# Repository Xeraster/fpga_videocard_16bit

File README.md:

# 16 bit fpga driven video card

### ISA interface ports:
- 0x423. settings register
- 0x426 - status register
- 0x428 address pointer low byte register (can also recieve 16 bit isa data cycles)
- 0x429 address pointer middle byte register
- 0x42A address pointer high byte register
- 0x42C data register

# what it does right now
It displays a 640x480 signal with 16 bit color depth. It also has a mostly working ISA interface. The video signal is far from perfect. This code is the synchronous version and is a lot buggier and doesn't work nearly as well. It is generally easy, with the synchronous version, to EITHER solve screen wobble OR incorrect colors but not both. In this particular git push, the colors get incorrect and messed up but screen wobble artifacts happen extremely rarely.

The pixel clock is 25.175MHz and the pll clock is 75.525MHz.

Here is an example of it outputting something. The asynchronous pll clock version has a terrible screen wobble bug (as the only major bug) so do not be fooled by what appears to be a good signal.

Here is a test pattern

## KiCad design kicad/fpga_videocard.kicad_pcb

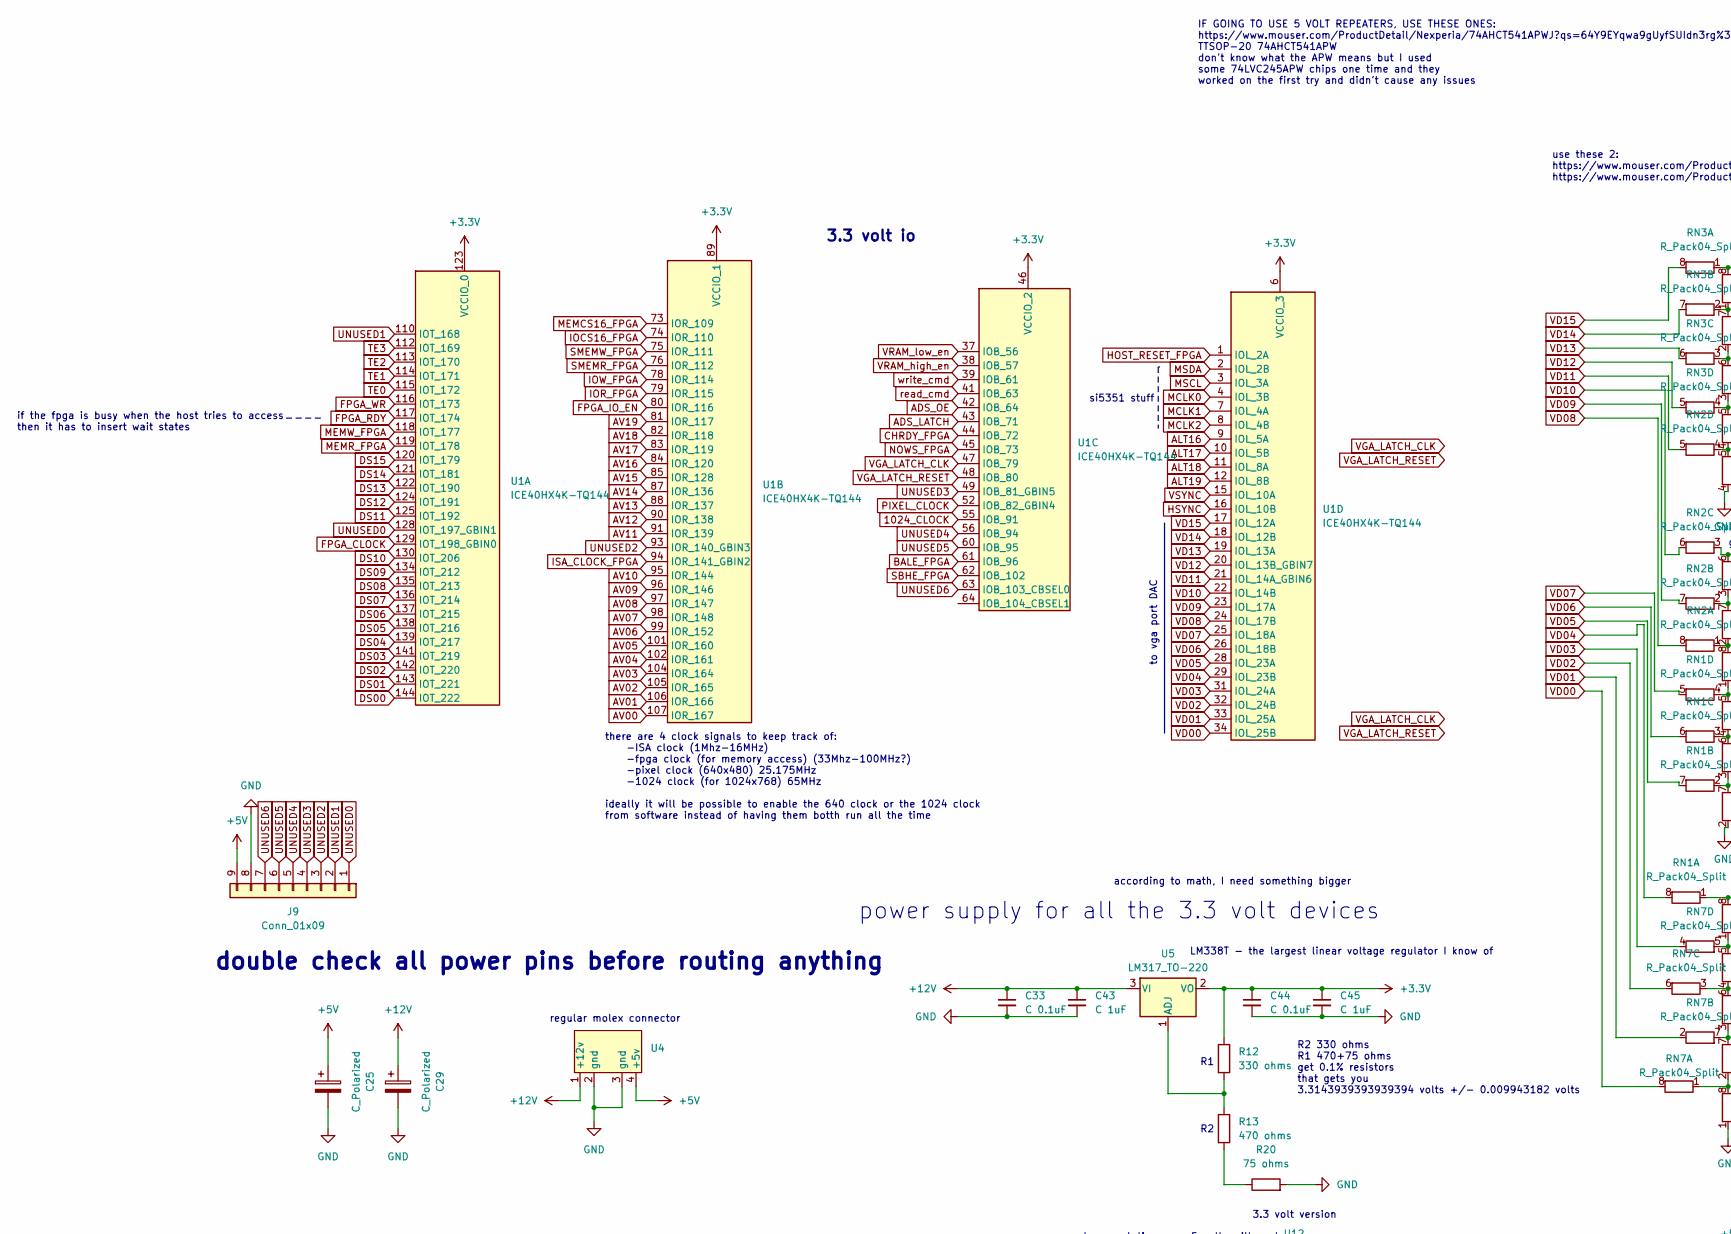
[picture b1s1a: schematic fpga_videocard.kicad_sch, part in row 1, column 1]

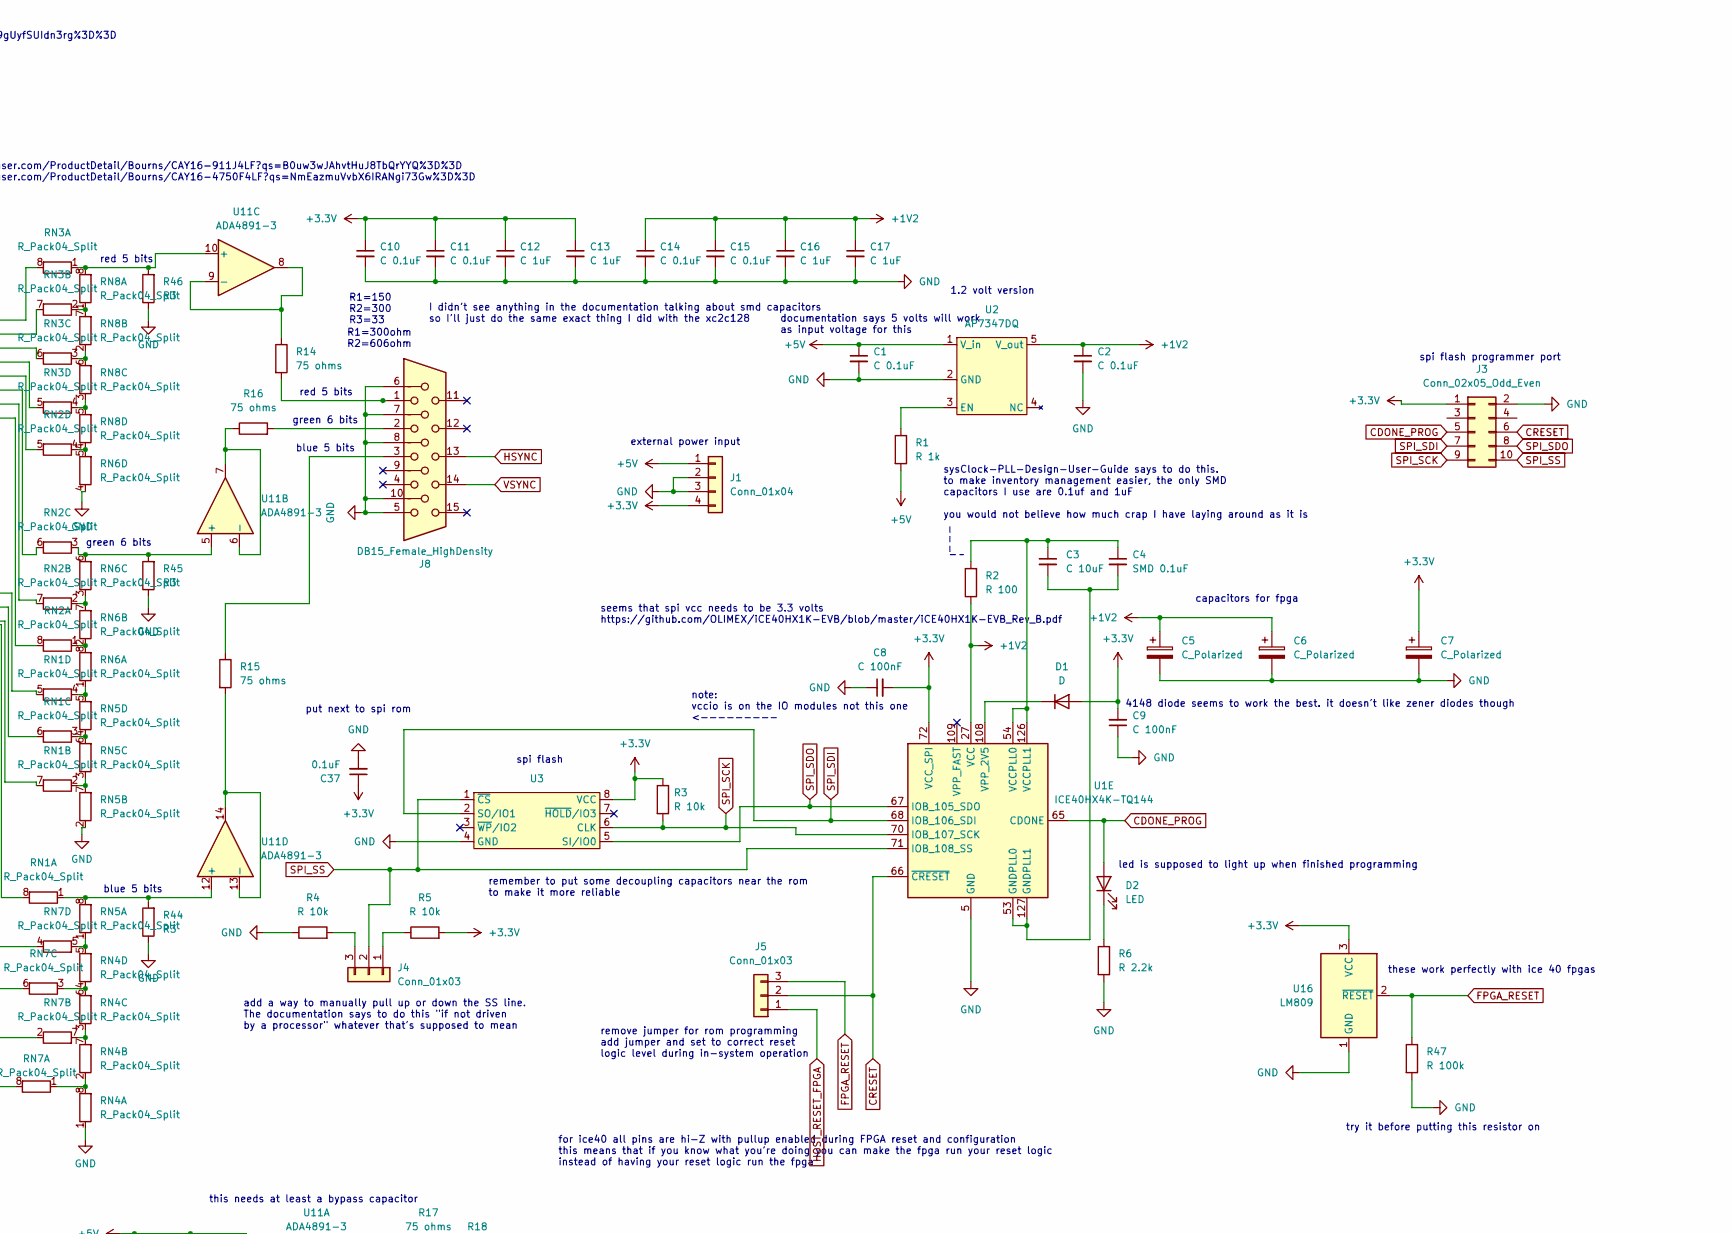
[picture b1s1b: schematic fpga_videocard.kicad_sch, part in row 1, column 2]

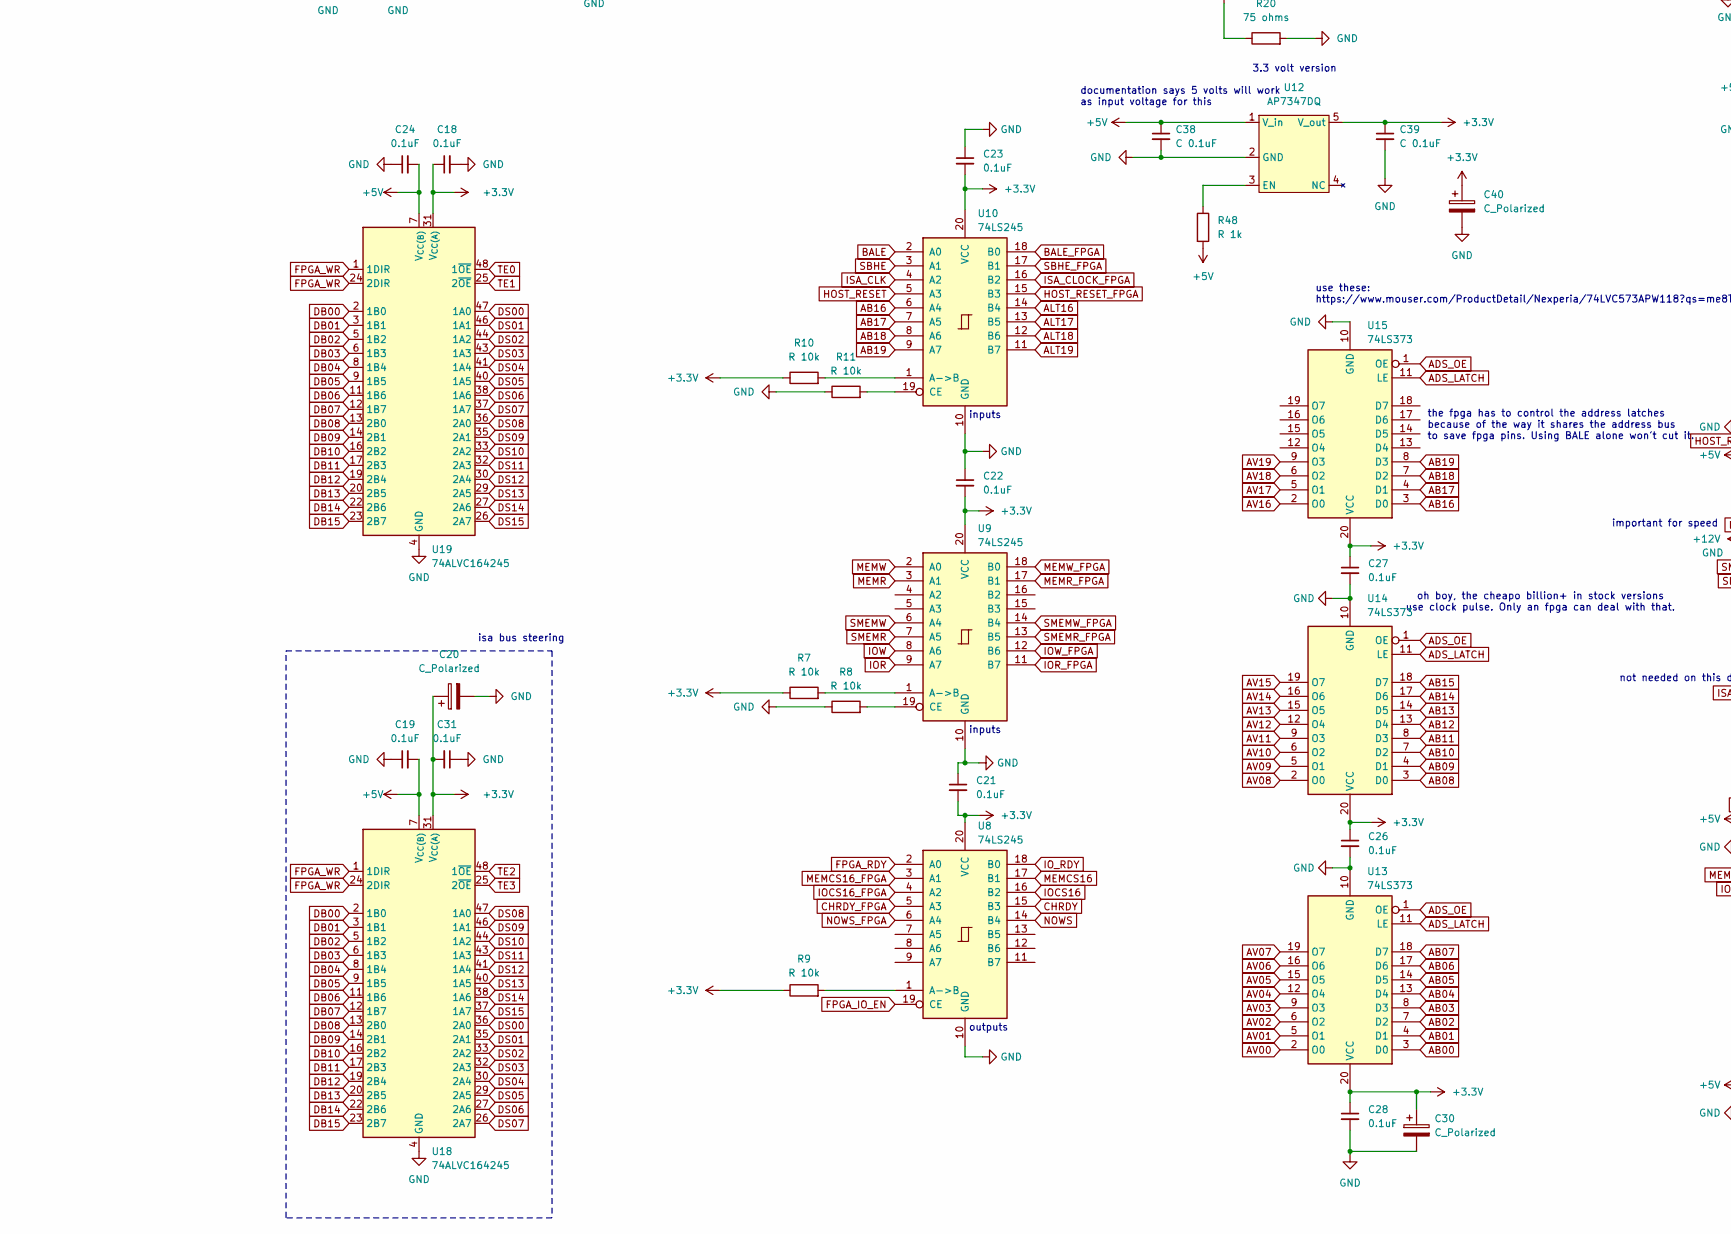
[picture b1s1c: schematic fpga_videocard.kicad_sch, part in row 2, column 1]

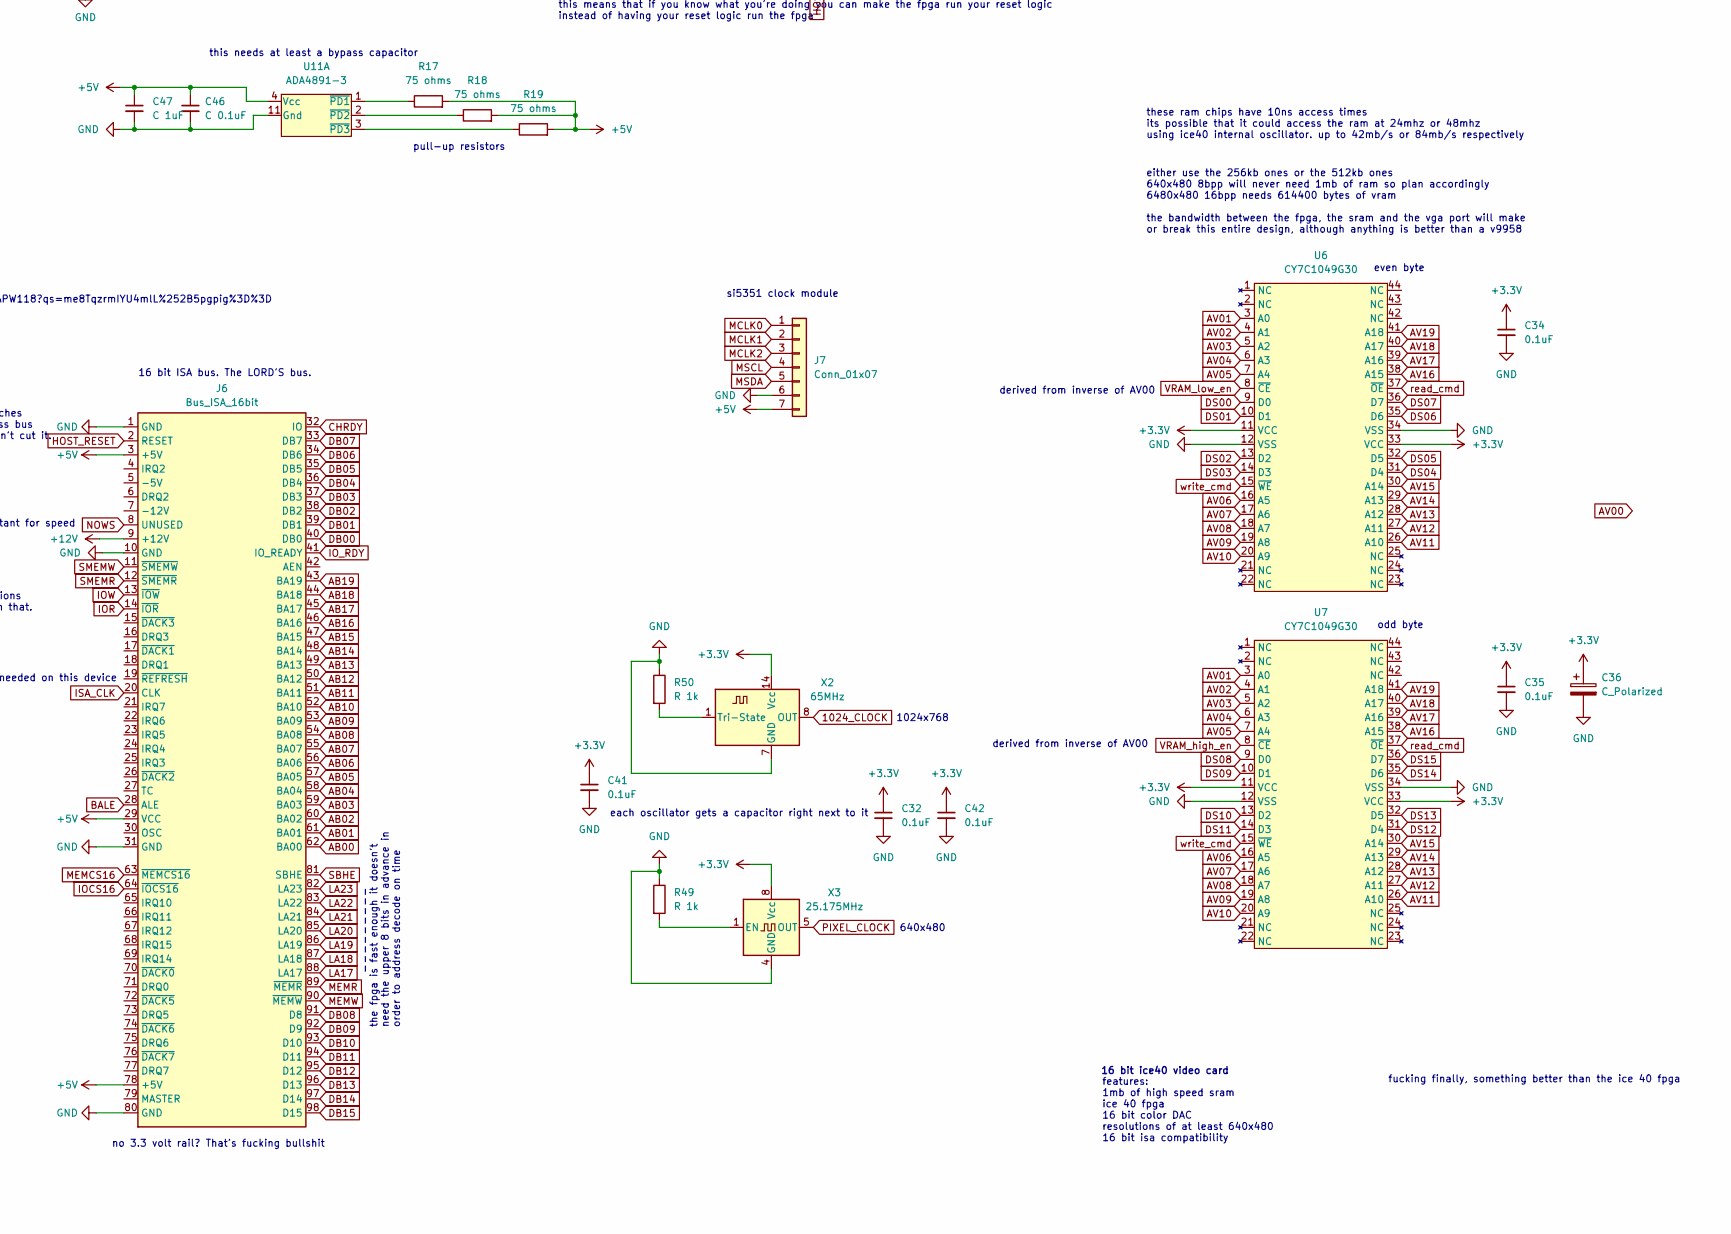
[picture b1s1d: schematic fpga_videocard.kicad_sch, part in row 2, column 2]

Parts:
C1, C2, C10, C11, C14, C15, C38, C39: C 0.1uF; C_1206_3216Metric
C3: C 10uF; C_1206_3216Metric
C4: SMD 0.1uF; C_1206_3216Metric
C5, C6, C7, C20, C25, C29, C40: C_Polarized; CP_Radial_D5.0mm_P2.50mm
C8, C9: C 100nF; C_Disc_D4.3mm_W1.9mm_P5.00mm
C12, C13, C16, C17: C 1uF; C_1206_3216Metric
C18, C19, C21, C22, C23, C24, C26, C27, C28, C31, C32, C34, C35, C37, C41, C42: 0.1uF; C_1206_3216Metric_Pad1.33x1.80mm_HandSolder
C30, C36: C_Polarized; CP_Radial_D4.0mm_P2.00mm
C33, C44, C46: C 0.1uF; C_1206_3216Metric_Pad1.33x1.80mm_HandSolder
C43, C45, C47: C 1uF; C_1206_3216Metric_Pad1.33x1.80mm_HandSolder
D1: D; D_DO-34_SOD68_P7.62mm_Horizontal
D2: LED; LED_D5.0mm
J1: Conn_01x04; PinHeader_1x04_P2.54mm_Vertical
J3: Conn_02x05_Odd_Even; PinHeader_2x05_P2.54mm_Vertical
J4, J5: Conn_01x03; PinHeader_1x03_P2.54mm_Vertical
J6: Bus_ISA_16bit; BUS_AT
J7: Conn_01x07; PinHeader_1x07_P2.54mm_Vertical
J8: DB15_Female_HighDensity; DSUB-15-HD_Female_Horizontal_P2.29x1.98mm_EdgePinOffset3.03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
J9: Conn_01x09; PinHeader_1x09_P2.54mm_Vertical
R1, R48, R49, R50: R 1k; R_Axial_DIN0207_L6.3mm_D2.5mm_P10.16mm_Horizontal
R2: R 100; R_Axial_DIN0207_L6.3mm_D2.5mm_P10.16mm_Horizontal
R3, R4, R5, R7, R8, R9, R10, R11: R 10k; R_0805_2012Metric_Pad1.20x1.40mm_HandSolder
R6: R 2.2k; R_Axial_DIN0207_L6.3mm_D2.5mm_P10.16mm_Horizontal
R12: 330 ohms; R_0805_2012Metric_Pad1.20x1.40mm_HandSolder
R13: 470 ohms; R_0805_2012Metric_Pad1.20x1.40mm_HandSolder
R14, R15, R16, R17, R18, R19, R20: 75 ohms; R_0805_2012Metric_Pad1.20x1.40mm_HandSolder
R44, R45, R46: R3; R_0805_2012Metric_Pad1.20x1.40mm_HandSolder
R47: R 100k; R_Axial_DIN0207_L6.3mm_D2.5mm_P10.16mm_Horizontal
RN1, RN2, RN3, RN4, RN5, RN6, RN7, RN8: R_Pack04_Split; R_Array_Convex_4x1206
U1: ICE40HX4K-TQ144; TQFP-144_20x20mm_P0.5mm
U2, U12: AP7347DQ; SOT-23-5
U3: SOIC-8_5.275x5.275mm_P1.27mm
U4: Mouser_Molex
U5: LM317_TO-220; TO-220-3_Vertical
U6, U7: CY7C1049G30; TSOP-44
U8, U9, U10: 74LS245; TSSOP-20_4.4x6.5mm_P0.65mm
U11: ADA4891-3; TSSOP-14_4.4x5mm_P0.65mm
U13, U14, U15: 74LS373; TSSOP-20_4.4x6.5mm_P0.65mm
U16: LM809; SOT-23
U18, U19: 74ALVC164245; TSSOP-48_6.1x12.5mm_P0.5mm
X2: 65MHz; Oscillator_DIP-14
X3: 25.175MHz; Oscillator_DIP-8

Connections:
1024_CLOCK: U1.55 (IOB_91), X2.8 (OUT)
+1V2: C2.1, C5.1, C6.1, C14.1, C15.1, C16.1, C17.1, R2.1, U1.27 (VCC), U1.40 (VCC), U1.92 (VCC), U1.111 (VCC), U2.5 (V_out)
+3.3V: C7.1, C8.2, C9.2, C10.1, C11.1, C12.1, C13.1, C18.1, C20.1, C21.2, C22.2, C23.2, C26.1, C27.1, C28.1, C30.1, C31.2, C32.1, C34.1, C35.1, C36.1, C37.1, C39.1, C40.1, C41.1, C42.1, C44.1, C45.1, D1.2 (A), J1.4, J3.1, R3.1, R5.2, R7.1, R9.1, R10.1, R12.1, U1.6 (VCCIO_3), U1.30 (VCCIO_3), U1.46 (VCCIO_2), U1.57 (VCCIO_2), U1.72 (VCC_SPI), U1.89 (VCCIO_1), U1.100 (VCCIO_1), U1.123 (VCCIO_0), U1.131 (VCCIO_0), U3.8 (VCC), U5.2 (VO), U6.11 (VCC), U6.33 (VCC), U7.11 (VCC), U7.33 (VCC), U8.20 (VCC), U9.20 (VCC), U10.20 (VCC), U12.5 (V_out), U13.20 (VCC), U14.20 (VCC), U15.20 (VCC), U16.3 (VCC), U18.31 (V_{CC(A)}), U18.42 (V_{CC(A)}), U19.31 (V_{CC(A)}), U19.42 (V_{CC(A)}), X2.14 (Vcc), X3.8 (Vcc)
+5V: C1.1, C19.2, C24.2, C25.1, C38.1, C46.1, C47.1, J1.1, J6.3 (+5V), J6.29 (VCC), J6.78 (+5V), J7.7, J9.9, R1.2, R17.2, R18.2, R19.2, R48.2, U2.1 (V_in), U4.4 (+5v), U11.4 (Vcc), U12.1 (V_in), U18.7 (V_{CC(B)}), U18.18 (V_{CC(B)}), U19.7 (V_{CC(B)}), U19.18 (V_{CC(B)})
+12V: C29.1, C33.1, C43.1, J6.9 (+12V), U4.1 (+12v), U5.3 (VI)
AB00: J6.62 (BA00), U13.3 (D0)
AB01: J6.61 (BA01), U13.4 (D1)
AB02: J6.60 (BA02), U13.7 (D2)
AB03: J6.59 (BA03), U13.8 (D3)
AB04: J6.58 (BA04), U13.13 (D4)
AB05: J6.57 (BA05), U13.14 (D5)
AB06: J6.56 (BA06), U13.17 (D6)
AB07: J6.55 (BA07), U13.18 (D7)
AB08: J6.54 (BA08), U14.3 (D0)
AB09: J6.53 (BA09), U14.4 (D1)
AB10: J6.52 (BA10), U14.7 (D2)
AB11: J6.51 (BA11), U14.8 (D3)
AB12: J6.50 (BA12), U14.13 (D4)
AB13: J6.49 (BA13), U14.14 (D5)
AB14: J6.48 (BA14), U14.17 (D6)
AB15: J6.47 (BA15), U14.18 (D7)
AB16: J6.46 (BA16), U10.6 (A4), U15.3 (D0)
AB17: J6.45 (BA17), U10.7 (A5), U15.4 (D1)
AB18: J6.44 (BA18), U10.8 (A6), U15.7 (D2)
AB19: J6.43 (BA19), U10.9 (A7), U15.8 (D3)
ADS_LATCH: U1.43 (IOB_71), U13.11 (LE), U14.11 (LE), U15.11 (LE)
ADS_OE: U1.42 (IOB_64), U13.1 (OE), U14.1 (OE), U15.1 (OE)
ALT16: U1.9 (IOL_5A), U10.14 (B4)
ALT17: U1.10 (IOL_5B), U10.13 (B5)
ALT18: U1.11 (IOL_8A), U10.12 (B6)
ALT19: U1.12 (IOL_8B), U10.11 (B7)
AV00: U1.107 (IOR_167), U13.2 (O0)
AV01: U1.106 (IOR_166), U6.3 (A0), U7.3 (A0), U13.5 (O1)
AV02: U1.105 (IOR_165), U6.4 (A1), U7.4 (A1), U13.6 (O2)
AV03: U1.104 (IOR_164), U6.5 (A2), U7.5 (A2), U13.9 (O3)
AV04: U1.102 (IOR_161), U6.6 (A3), U7.6 (A3), U13.12 (O4)
AV05: U1.101 (IOR_160), U6.7 (A4), U7.7 (A4), U13.15 (O5)
AV06: U1.99 (IOR_152), U6.16 (A5), U7.16 (A5), U13.16 (O6)
AV07: U1.98 (IOR_148), U6.17 (A6), U7.17 (A6), U13.19 (O7)
AV08: U1.97 (IOR_147), U6.18 (A7), U7.18 (A7), U14.2 (O0)
AV09: U1.96 (IOR_146), U6.19 (A8), U7.19 (A8), U14.5 (O1)
AV10: U1.95 (IOR_144), U6.20 (A9), U7.20 (A9), U14.6 (O2)
AV11: U1.91 (IOR_139), U6.26 (A10), U7.26 (A10), U14.9 (O3)
AV12: U1.90 (IOR_138), U6.27 (A11), U7.27 (A11), U14.12 (O4)
AV13: U1.88 (IOR_137), U6.28 (A12), U7.28 (A12), U14.15 (O5)
AV14: U1.87 (IOR_136), U6.29 (A13), U7.29 (A13), U14.16 (O6)
AV15: U1.85 (IOR_128), U6.30 (A14), U7.30 (A14), U14.19 (O7)
AV16: U1.84 (IOR_120), U6.38 (A15), U7.38 (A15), U15.2 (O0)
AV17: U1.83 (IOR_119), U6.39 (A16), U7.39 (A16), U15.5 (O1)
AV18: U1.82 (IOR_118), U6.40 (A17), U7.40 (A17), U15.6 (O2)
AV19: U1.81 (IOR_117), U6.41 (A18), U7.41 (A18), U15.9 (O3)
BALE: J6.28 (ALE), U10.2 (A0)
BALE_FPGA: U1.61 (IOB_96), U10.18 (B0)
CDONE_PROG: D2.2 (A), J3.5, U1.65 (CDONE)
CHRDY: J6.32 (IO), U8.15 (B3)
CHRDY_FPGA: U1.44 (IOB_72), U8.5 (A3)
CRESET: J3.6, J5.2, U1.66 (~CRESET)
DB00: J6.40 (DB0), U18.2 (1B0), U19.2 (1B0)
DB01: J6.39 (DB1), U18.3 (1B1), U19.3 (1B1)
DB02: J6.38 (DB2), U18.5 (1B2), U19.5 (1B2)
DB03: J6.37 (DB3), U18.6 (1B3), U19.6 (1B3)
DB04: J6.36 (DB4), U18.8 (1B4), U19.8 (1B4)
DB05: J6.35 (DB5), U18.9 (1B5), U19.9 (1B5)
DB06: J6.34 (DB6), U18.11 (1B6), U19.11 (1B6)
DB07: J6.33 (DB7), U18.12 (1B7), U19.12 (1B7)
DB08: J6.91 (D8), U18.13 (2B0), U19.13 (2B0)
DB09: J6.92 (D9), U18.14 (2B1), U19.14 (2B1)
DB10: J6.93 (D10), U18.16 (2B2), U19.16 (2B2)
DB11: J6.94 (D11), U18.17 (2B3), U19.17 (2B3)
DB12: J6.95 (D12), U18.19 (2B4), U19.19 (2B4)
DB13: J6.96 (D13), U18.20 (2B5), U19.20 (2B5)
DB14: J6.97 (D14), U18.22 (2B6), U19.22 (2B6)
DB15: J6.98 (D15), U18.23 (2B7), U19.23 (2B7)
DS00: U1.144 (IOT_222), U6.9 (D0), U18.36 (2A0), U19.47 (1A0)
DS01: U1.143 (IOT_221), U6.10 (D1), U18.35 (2A1), U19.46 (1A1)
DS02: U1.142 (IOT_220), U6.13 (D2), U18.33 (2A2), U19.44 (1A2)
DS03: U1.141 (IOT_219), U6.14 (D3), U18.32 (2A3), U19.43 (1A3)
DS04: U1.139 (IOT_217), U6.31 (D4), U18.30 (2A4), U19.41 (1A4)
DS05: U1.138 (IOT_216), U6.32 (D5), U18.29 (2A5), U19.40 (1A5)
DS06: U1.137 (IOT_215), U6.35 (D6), U18.27 (2A6), U19.38 (1A6)
DS07: U1.136 (IOT_214), U6.36 (D7), U18.26 (2A7), U19.37 (1A7)
DS08: U1.135 (IOT_213), U7.9 (D0), U18.47 (1A0), U19.36 (2A0)
DS09: U1.134 (IOT_212), U7.10 (D1), U18.46 (1A1), U19.35 (2A1)
DS10: U1.130 (IOT_206), U7.13 (D2), U18.44 (1A2), U19.33 (2A2)
DS11: U1.125 (IOT_192), U7.14 (D3), U18.43 (1A3), U19.32 (2A3)
DS12: U1.124 (IOT_191), U7.31 (D4), U18.41 (1A4), U19.30 (2A4)
DS13: U1.122 (IOT_190), U7.32 (D5), U18.40 (1A5), U19.29 (2A5)
DS14: U1.121 (IOT_181), U7.35 (D6), U18.38 (1A6), U19.27 (2A6)
DS15: U1.120 (IOT_179), U7.36 (D7), U18.37 (1A7), U19.26 (2A7)
FPGA_CLOCK: U1.129 (IOT_198_GBIN0)
FPGA_IO_EN: U1.80 (IOR_116), U8.19 (CE)
FPGA_RDY: U1.117 (IOT_174), U8.2 (A0)
FPGA_RESET: J5.3, R47.1, U16.2 (~RESET)
FPGA_WR: U1.116 (IOT_173), U18.1 (1DIR), U18.24 (2DIR), U19.1 (1DIR), U19.24 (2DIR)
GND: C1.2, C2.2, C5.2, C6.2, C7.2, C8.1, C9.1, C10.2, C11.2, C12.2, C13.2, C14.2, C15.2, C16.2, C17.2, C18.2, C19.1, C20.2, C21.1, C22.1, C23.1, C24.1, C25.2, C26.2, C27.2, C28.2, C29.2, C30.2, C31.1, C32.2, C33.2, C34.2, C35.2, C36.2, C37.2, C38.2, C39.2, C40.2, C41.2, C42.2, C43.2, C44.2, C45.2, C46.2, C47.2, J1.2, J1.3, J3.2, J6.1 (GND), J6.10 (GND), J6.31 (GND), J6.80 (GND), J7.6, J8.5, J8.6, J8.7, J8.8, J8.10, J9.8, R4.1, R6.2, R8.1, R11.1, R20.2, R44.1, R45.1, R46.1, R47.2, R49.1, R50.1, RN4.1 (R1.1), RN5.2 (R2.1), RN6.4 (R4.1), U1.5 (GND), U1.13 (GND), U1.14 (GND), U1.59 (GND), U1.69 (GND), U1.86 (GND), U1.103 (GND), U1.132 (GND), U1.140 (GND), U2.2 (GND), U3.4 (GND), U4.2 (gnd), U4.3 (gnd), U6.12 (VSS), U6.34 (VSS), U7.12 (VSS), U7.34 (VSS), U8.10 (GND), U9.10 (GND), U10.10 (GND), U11.11 (Gnd), U12.2 (GND), U13.10 (GND), U14.10 (GND), U15.10 (GND), U16.1 (GND), U18.4 (GND), U18.10 (GND), U18.15 (GND), U18.21 (GND), U18.28 (GND), U18.34 (GND), U18.39 (GND), U18.45 (GND), U19.4 (GND), U19.10 (GND), U19.15 (GND), U19.21 (GND), U19.28 (GND), U19.34 (GND), U19.39 (GND), U19.45 (GND), X2.7 (GND), X3.4 (GND)
HOST_RESET: J6.2 (RESET), U10.5 (A3)
HOST_RESET_FPGA: J5.1, U1.1 (IOL_2A), U10.15 (B3)
HSYNC: J8.13, U1.16 (IOL_10B)
IOCS16: J6.64 (~IOCS16), U8.16 (B2)
IOCS16_FPGA: U1.74 (IOR_110), U8.4 (A2)
IOR: J6.14 (~IOR), U9.9 (A7)
IOR_FPGA: U1.79 (IOR_115), U9.11 (B7)
IOW: J6.13 (~IOW), U9.8 (A6)
IOW_FPGA: U1.78 (IOR_114), U9.12 (B6)
IO_RDY: J6.41 (IO_READY), U8.18 (B0)
ISA_CLK: J6.20 (CLK), U10.4 (A2)
ISA_CLOCK_FPGA: U1.94 (IOR_141_GBIN2), U10.16 (B2)
LA17: J6.88 (LA17)
LA18: J6.87 (LA18)
LA19: J6.86 (LA19)
LA20: J6.85 (LA20)
LA21: J6.84 (LA21)
LA22: J6.83 (LA22)
LA23: J6.82 (LA23)
MCLK0: J7.1, U1.4 (IOL_3B)
MCLK1: J7.2, U1.7 (IOL_4A)
MCLK2: J7.3, U1.8 (IOL_4B)
MEMCS16: J6.63 (~MEMCS16), U8.17 (B1)
MEMCS16_FPGA: U1.73 (IOR_109), U8.3 (A1)
MEMR: J6.89 (~MEMR), U9.3 (A1)
MEMR_FPGA: U1.119 (IOT_178), U9.17 (B1)
MEMW: J6.90 (~MEMW), U9.2 (A0)
MEMW_FPGA: U1.118 (IOT_177), U9.18 (B0)
MSCL: J7.4, U1.3 (IOL_3A)
MSDA: J7.5, U1.2 (IOL_2B)
NOWS: J6.8 (UNUSED), U8.14 (B4)
NOWS_FPGA: U1.45 (IOB_73), U8.6 (A4)
unnamed: D1.1 (K), U1.108 (VPP_2V5)
unnamed: D2.1 (K), R6.1
unnamed: J4.1, R5.1
unnamed: J4.3, R4.2
unnamed: J8.1, R14.2
unnamed: J8.2, R16.2
unnamed: J8.3, R15.1
unnamed: R13.2, R20.1
unnamed: R44.2, RN1.1 (R1.1), RN5.8 (R1.2), U11.12 (+)
unnamed: RN1.2 (R2.1), RN5.3 (R3.1), RN5.7 (R2.2)
unnamed: RN1.3 (R3.1), RN5.4 (R4.1), RN5.6 (R3.2)
unnamed: RN1.4 (R4.1), RN5.5 (R4.2), RN6.1 (R1.1)
unnamed: RN2.1 (R1.1), RN6.2 (R2.1), RN6.8 (R1.2)
unnamed: RN2.2 (R2.1), RN6.3 (R3.1), RN6.7 (R2.2)
unnamed: R45.2, RN2.3 (R3.1), RN6.6 (R3.2), U11.5 (+)
unnamed: RN2.4 (R4.1), RN6.5 (R4.2), RN8.4 (R4.1)
unnamed: R46.2, RN3.1 (R1.1), RN8.8 (R1.2), U11.10 (+)
unnamed: RN3.2 (R2.1), RN8.1 (R1.1), RN8.7 (R2.2)
unnamed: RN3.3 (R3.1), RN8.2 (R2.1), RN8.6 (R3.2)
unnamed: RN3.4 (R4.1), RN8.3 (R3.1), RN8.5 (R4.2)
unnamed: RN4.2 (R2.1), RN4.8 (R1.2), RN7.1 (R1.1)
unnamed: RN4.3 (R3.1), RN4.7 (R2.2), RN7.7 (R2.2)
unnamed: RN4.4 (R4.1), RN4.6 (R3.2), RN7.3 (R3.1)
unnamed: RN4.5 (R4.2), RN5.1 (R1.1), RN7.5 (R4.2)
unnamed: C3.2, C4.2, U1.53 (GNDPLL0), U1.127 (GNDPLL1)
unnamed: C3.1, C4.1, R2.2, U1.54 (VCCPLL0), U1.126 (VCCPLL1)
unnamed: R1.1, U2.3 (EN)
unnamed: R12.2, R13.1, U5.1 (ADJ)
unnamed: R9.2, U8.1 (A->B)
unnamed: R7.2, U9.1 (A->B)
unnamed: R8.2, U9.19 (CE)
unnamed: R10.2, U10.1 (A->B)
unnamed: R11.2, U10.19 (CE)
unnamed: R17.1, U11.1 (~PD1)
unnamed: R18.1, U11.2 (~PD2)
unnamed: R19.1, U11.3 (~PD3)
unnamed: R16.1, U11.6 (-), U11.7
unnamed: R14.1, U11.8, U11.9 (-)
unnamed: R15.2, U11.13 (-), U11.14
unnamed: R48.1, U12.3 (EN)
unnamed: R50.2, X2.1 (Tri-State)
unnamed: R49.2, X3.1 (EN)
PIXEL_CLOCK: U1.52 (IOB_82_GBIN4), X3.5 (OUT)
SBHE: J6.81 (SBHE), U10.3 (A1)
SBHE_FPGA: U1.62 (IOB_102), U10.17 (B1)
SMEMR: J6.12 (~SMEMR), U9.7 (A5)
SMEMR_FPGA: U1.76 (IOR_112), U9.13 (B5)
SMEMW: J6.11 (~SMEMW), U9.6 (A4)
SMEMW_FPGA: U1.75 (IOR_111), U9.14 (B4)
SPI_SCK: J3.9, R3.2, U1.70 (IOB_107_SCK), U3.6 (CLK)
SPI_SDI: J3.7, U1.68 (IOB_106_SDI), U3.2 (SO/IO1)
SPI_SDO: J3.8, U1.67 (IOB_105_SDO), U3.5 (SI/IO0)
SPI_SS: J3.10, J4.2, U1.71 (IOB_108_SS), U3.1 (~CS)
TE0: U1.115 (IOT_172), U19.48 (1~OE)
TE1: U1.114 (IOT_171), U19.25 (2~OE)
TE2: U1.113 (IOT_170), U18.48 (1~OE)
TE3: U1.112 (IOT_169), U18.25 (2~OE)
UNUSED0: J9.1, U1.128 (IOT_197_GBIN1)
UNUSED1: J9.2, U1.110 (IOT_168)
UNUSED2: J9.3, U1.93 (IOR_140_GBIN3)
UNUSED3: J9.4, U1.49 (IOB_81_GBIN5)
UNUSED4: J9.5, U1.56 (IOB_94)
UNUSED5: J9.6, U1.60 (IOB_95)
UNUSED6: J9.7, U1.63 (IOB_103_CBSEL0)
VD00: RN7.8 (R1.2), U1.34 (IOL_25B)
VD01: RN7.2 (R2.1), U1.33 (IOL_25A)
VD02: RN7.6 (R3.2), U1.32 (IOL_24B)
VD03: RN7.4 (R4.1), U1.31 (IOL_24A)
VD04: RN1.8 (R1.2), U1.29 (IOL_23B)
VD05: RN1.7 (R2.2), U1.28 (IOL_23A)
VD06: RN1.6 (R3.2), U1.26 (IOL_18B)
VD07: RN1.5 (R4.2), U1.25 (IOL_18A)
VD08: RN2.8 (R1.2), U1.24 (IOL_17B)
VD09: RN2.7 (R2.2), U1.23 (IOL_17A)
VD10: RN2.6 (R3.2), U1.22 (IOL_14B)
VD11: RN2.5 (R4.2), U1.21 (IOL_14A_GBIN6)
VD12: RN3.5 (R4.2), U1.20 (IOL_13B_GBIN7)
VD13: RN3.6 (R3.2), U1.19 (IOL_13A)
VD14: RN3.7 (R2.2), U1.18 (IOL_12B)
VD15: RN3.8 (R1.2), U1.17 (IOL_12A)
VGA_LATCH_CLK: U1.47 (IOB_79)
VGA_LATCH_RESET: U1.48 (IOB_80)
VRAM_high_en: U1.38 (IOB_57), U7.8 (~CE)
VRAM_low_en: U1.37 (IOB_56), U6.8 (~CE)
VSYNC: J8.14, U1.15 (IOL_10A)
read_cmd: U1.41 (IOB_63), U6.37 (~OE), U7.37 (~OE)
write_cmd: U1.39 (IOB_61), U6.15 (~WE), U7.15 (~WE)

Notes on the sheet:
LM338T - the largest linear voltage regulator I know of
these work perfectly with ice 40 fpgas
red 5 bits
isa bus steering
the fpga has to control the address latches because of the way it shares the address bus to save fpga pins. Using BALE alone won't cut it.
IF GOING TO USE 5 VOLT REPEATERS, USE THESE ONES: https://www.mouser.com/ProductDetail/Nexperia/74AHCT541APWJ?qs=64Y9EYqwa9gUyfSUIdn3rg%3D%3D TTSOP-20 74AHCT541APW don't know what the APW means but I used some 74LVC245APW chips one time and they worked on the first try and didn't cause any issues
even byte
remove jumper for rom programming add jumper and set to correct reset logic level during in-system operation
use these: https://www.mouser.com/ProductDetail/Nexperia/74LVC573APW118?qs=me8TqzrmIYU4mlL%252B5pgpig%3D%3D
these ram chips have 10ns access times its possible that it could access the ram at 24mhz or 48mhz using ice40 internal oscillator. up to 42mb/s or 84mb/s respectively
try it before putting this resistor on
R1=300ohm R2=606ohm
sysClock-PLL-Design-User-Guide says to do this. to make inventory management easier, the only SMD capacitors I use are 0.1uf and 1uF you would not believe how much crap I have laying around as it is
spi flash
si5351 stuff
according to math, I need something bigger
regular molex connector
this needs at least a bypass capacitor
to vga port DAC
fucking finally, something better than the ice 40 fpga
use these 2: https://www.mouser.com/ProductDetail/Bourns/CAY16-911J4LF?qs=B0uw3wJAhvtHuJ8TbQrYYQ%3D%3D https://www.mouser.com/ProductDetail/Bourns/CAY16-4750F4LF?qs=NmEazmuVvbX6IRANgi73Gw%3D%3D
no 3.3 volt rail? That's fucking bullshit
1.2 volt version
3.3 volt io
for ice40 all pins are hi-Z with pullup enabled during FPGA reset and configuration this means that if you know what you're doing you can make the fpga run your reset logic instead of having your reset logic run the fpga
blue 5 bits
not needed on this device
note: vccio is on the IO modules not this one <---------
either use the 256kb ones or the 512kb ones 640x480 8bpp will never need 1mb of ram so plan accordingly 6480x480 16bpp needs 614400 bytes of vram the bandwidth between the fpga, the sram and the vga port will make or break this entire design, although anything is better than a v9958
double check all power pins before routing anything
led is supposed to light up when finished programming
if the fpga is busy when the host tries to access then it has to insert wait states
external power input
inputs
16 bit ice40 video card
put next to spi rom
power supply for all the 3.3 volt devices
green 6 bits
seems that spi vcc needs to be 3.3 volts https://github.com/OLIMEX/iCE40HX1K-EVB/blob/master/iCE40HX1K-EVB_Rev_B.pdf
pull-up resistors

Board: 4 copper layers, 112 parts (0 on the bottom side), 204 nets, no tracks yet.

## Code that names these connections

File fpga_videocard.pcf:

set_io pixelClock 52
#set_io clock1024 55
set_io HOST_RESET 1
set_io HSYNC 16
set_io VSYNC 15

#vga output bits
set_io Red[0] 21    #VD11
set_io Red[1] 128    #use this pin instead because of a routing mistake
set_io Red[2] 19
set_io Red[3] 18
set_io Red[4] 17    #VD15

set_io Green[0] 28    #VD05
set_io Green[1] 26
set_io Green[2] 25
set_io Green[3] 24
set_io Green[4] 23
set_io Green[5] 22    #VD10

set_io Blue[0] 34    #VD00
set_io Blue[1] 33
set_io Blue[2] 32
set_io Blue[3] 31
set_io Blue[4] 29    #VD04

#vram address bus
set_io AV[0] 107
set_io AV[1] 106
set_io AV[2] 105
set_io AV[3] 104
set_io AV[4] 102
set_io AV[5] 101
set_io AV[6] 99
set_io AV[7] 98
set_io AV[8] 97
set_io AV[9] 96
set_io AV[10] 95
set_io AV[11] 91
set_io AV[12] 90
set_io AV[13] 88
set_io AV[14] 87
set_io AV[15] 85
set_io AV[16] 84
set_io AV[17] 83
set_io AV[18] 82
set_io AV[19] 81

#16 bit vram data bus
set_io DS[0] 144
set_io DS[1] 143
set_io DS[2] 142
set_io DS[3] 141
set_io DS[4] 139
set_io DS[5] 138
set_io DS[6] 137
set_io DS[7] 136
set_io DS[8] 135
set_io DS[9] 134
set_io DS[10] 130
set_io DS[11] 125
set_io DS[12] 124
set_io DS[13] 122
set_io DS[14] 121
set_io DS[15] 120

#sram chip control signals
set_io read_cmd 41
set_io write_cmd 39
set_io VRAM_low_en 37
set_io VRAM_high_en 38

set_io VGASCK 63
set_io VGAMOSI 60
set_io VGAMISO 56
set_io VGACS0 49

#just test ports, nothing special
set_io DEBUG0 93    #u2
set_io DEBUG1 110   #u1
set_io MCLK0 4
set_io MCLK1 7

#isa related stuff
set_io SBHE 62
set_io BALE 61
set_io IOCS16 74
set_io MEMCS16 73
set_io IOERR 44
set_io IO_RDY 117
set_io NOWS 45
set_io ADS_OE 42
set_io ADS_LATCH 43
set_io MEMR 119
set_io MEMW 118
set_io SMEMR 76
set_io SMEMW 75
set_io IOR 79
set_io IOW 78
set_io ISACLK 94

set_io FPGA_WR 116
set_io TE0 115
set_io TE1 114
set_io TE2 113
set_io TE3 112
set_io FASTCLK 55
set_io isa_ctrl_out_en 80

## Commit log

2025-01-04 made the comments more useful
2025-01-04 didn't upload the correct one (oops)
2025-01-04 took a better picture
2025-01-04 added the schematic
2025-01-05 found a way to make write cycles not mess everything up
2025-03-02 isa interface, write buffers, block swapping, and a universe of hard to fix bugs
2025-03-02 found a way to marginally reduce wobble
2025-03-03 reduced snow during non-device selection isa cycles by about 90%. however this caused more flickering bugs
2025-03-06 what I had at the end of the video is mostly what this is
2026-03-13 new changes
2026-03-14 preparation for isa-f protocol upgrade
2026-03-15 tried to make it work but was unsucessful
2026-03-16 got io to work
2026-03-16 did more stuff
2026-03-16 tried a small change tat might work, tried looking at verilator but its really complicated
2026-03-16 used ads oe for bus full detection
2026-03-16 added bus_free condition to write delay counter
2026-03-16 put everything back to the most optimal known configuration because the last thing didnt work
2026-03-17 started work on Verilator simulation
2026-03-18 verilator test. it doesnt work yet. imgoing to be pissed if its either not possible to get this to work or if the bug doesnt happen once it finally gets working
2026-03-18 got the verilator test to work
2026-03-19 latest changes
2026-03-19 added my thoughts about graphics acceleration
2026-03-19 partially fixed The Bug, or at least in the Verilator simulation
2026-03-19 applied and compiled some of the verilator changes into the hardware portion of the code
2026-03-19 did the thing that works the least shittily on the hardware
2026-03-19 found a way to fix more pixels that works with the limitations of the hardware
2026-03-19 removed thing that was making it not work, another approah to this problem needs to be found somehow
2026-03-20 did some stuff
2026-03-20 its at the point where verilator cant be of any further benefit
2026-03-20 made it only moderately worse than it was before i did this instead of way worse than before i did this. yay
2026-03-20 kind of got it working slightly less shittily than usual
2026-03-21 THIS IS NOT A DRILL. I FOUND A WAY TO IMPROVE IT SLIGHTLY
2026-03-21 improved things significant;y
2026-03-26 i dont know if its just me or this seems to reduce wobble somewhat.
2026-03-31 this now reflects the best known configuration
2026-03-31 set up the synchronous version of the code
